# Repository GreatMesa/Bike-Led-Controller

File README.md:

# Bike LED Controller
This project is sponsored by JLCPCB

## Introduction
The goal of this project is to add more customizability to bike lights. When I was looking though lights for my bike I found that there was a limited amount of colors and patterns I could use. I wanted to create lights and controllers so I could have a better understanding of what was going on in the controller in terms of current consumption and speed of the bike, things that also were not present in other controllers. In this project, I designed a custom bike ring + a custom led controller board so that I could have a greater level of control.

## Custom LED Ring
For the ring, I decided to split the base and top  of the ring into 8 seperate segments. This was due to the size of the ring being way to big for my bike & in terms of the print time & assembely ease, 8 segments seemed to do the best in those 2 categories. 

For the bottom, in order to connect the segments together, I decided to designed them so they would have a insert slot + a segment that goes into it. For the top, I ended up coating it in a layer of FLEX-SEAL in order to act as a water reppelent + a diffusior once I sanded it down to a degree. Here is one fully assmebled ring in action:

### LED Ring GIF

## Custom LED Controller
For the LED contoller, I had multiple goals in mine. The main goal I had was the ability for the contoller to convert a higher voltage input to a stable 5V. To do this, I used the TPS566238RQFR buck converter to convert the input voltage (designed for 2S) into 5V. I also used a AMS1117 to convert the 5V supply into 3.3V for the digital IC's and the ESP32. Speaking of digital IC's, I used 5 in this design, a INA236 to meausre the voltage, current, & power output of the controller, a TMP117 to measure the tempature of the board / enclousre enviroment, a BMI270 to measure the speed of the bike for custom effects, a SN74LVC2T45DCUR to convert the ESP32's 3.3V logic into a usable 5V logic level for the LED, and last but not least the CP2102N to allow communication between the USB pherephial and the ESP32 via UART. Here are the schematics, PCB layouts, & the 3D view.

### Schematic

### PCB Layout

### 3D View

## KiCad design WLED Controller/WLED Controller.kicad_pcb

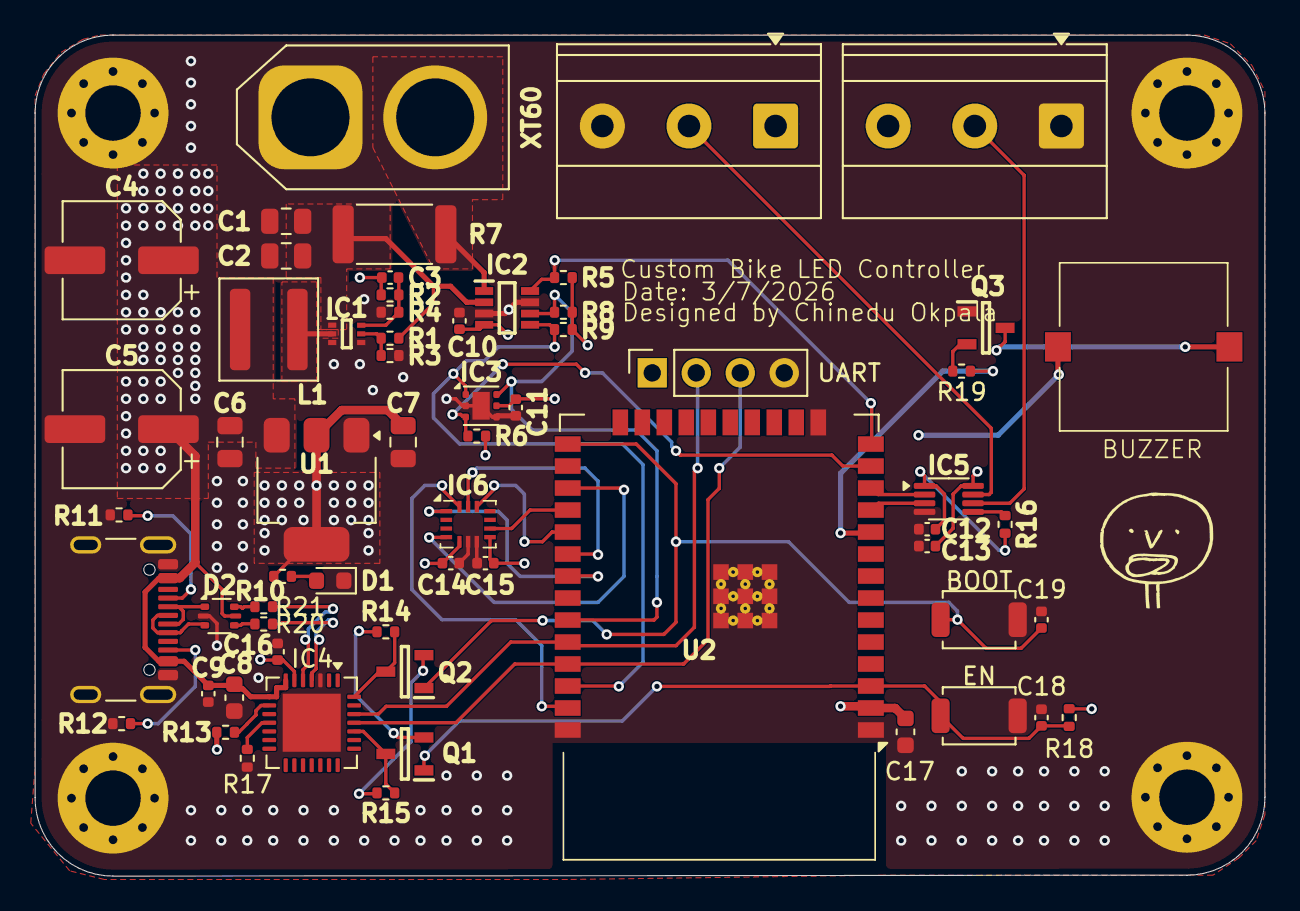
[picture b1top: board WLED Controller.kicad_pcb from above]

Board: 4 copper layers, 71.0 x 48.6 mm, 66 parts (0 on the bottom side), 45 nets.

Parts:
BOOT: Boot Switch; SW_SPST_TS-1088-xR025
BZ1: Buzzer; CMI97050380SMTTR
C1, C2: 22uF; C_0805_2012Metric
C3: 33pF; C_0402_1005Metric
C4, C5: 68uF; CP_Elec_6.3x5.8
C6, C7: 10uF; C_0805_2012Metric
C8, C17: 4.7uF; C_0603_1608Metric
C9, C10, C11, C12, C13, C14, C15, C16, C18, C19: 100nF; C_0402_1005Metric
D1: LED; LED_0603_1608Metric
D2: TVS; SOT-666
EN: Enable Switch; SW_SPST_TS-1088-xR025
H1: M1; MountingHole_3.2mm_M3_Pad_Via
H2: M2; MountingHole_3.2mm_M3_Pad_Via
H3: M3; MountingHole_3.2mm_M3_Pad_Via
H4: M4; MountingHole_3.2mm_M3_Pad_Via
IC1: TPS565242DRLR; SOTFL50P160X60-6N
IC2: INA236AIDDFR; SOP65P280X110-8N
IC3: TMP117xxDRV; WSON-6-1EP_2x2mm_P0.65mm_EP1x1.6mm
IC4: CP2102N-Axx-xQFN28; QFN-28-1EP_5x5mm_P0.5mm_EP3.35x3.35mm
IC5: SN74LVC2T45DCUR; VSSOP-8_2.3x2mm_P0.5mm
IC6: BMI270; Bosch_LGA-14_3x2.5mm_P0.5mm
J1, J2: Conn_01x03; TerminalBlock_Phoenix_MKDS-1,5-3_1x03_P5.00mm_Horizontal
J3: USB_C_Receptacle_USB2.0_14P; USB_C_Receptacle_GCT_USB4105-xx-A_16P_TopMnt_Horizontal
L1: 2.2uH; L_Coilcraft_XAL5030-XXX
Q1, Q2, Q3: NPN; SOT95P240X115-3N
R1: 100k; R_0402_1005Metric
R2: 220k; R_0402_1005Metric
R3: 33.3k; R_0402_1005Metric
R4: 30k; R_0402_1005Metric
R5, R6, R8, R9, R16, R17: 4.7k; R_0402_1005Metric
R7: 0.01; R_2512_6332Metric
R10, R13, R14, R15, R18: 10k; R_0402_1005Metric
R11, R12: 5.1k; R_0402_1005Metric
R19: 1k; R_0402_1005Metric
R20, R21: 22; R_0402_1005Metric
U1: AP1117-33; SOT-223-3_TabPin2
U2: ESP32-WROOM-32E
UART: UART; PinSocket_1x04_P2.54mm_Vertical
XT60: XT-60; AMASS_XT60-F_1x02_P7.20mm_Vertical

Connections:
+3.3V: BZ1.1 (+), C7.1, C10.1, C11.1, C12.1, C14.1, C15.1, C16.1, C17.1, IC2.4 (VS), IC3.5 (V+), IC4.6 (VDD), IC5.1 (VCCA), IC6.5 (VDDIO), IC6.8 (VDD), R5.1, R6.1, R8.1, R9.1, R10.1, R13.1, R16.1, R18.2, U1.2 (VO), U2.2 (VDD), UART.1
+5V: C3.1, C4.1, C5.1, C6.1, C8.1, C9.1, C13.1, D2.5 (VBUS), IC4.7 (VREGIN), IC4.8 (VBUS), IC5.8 (VCCB), J1.1, J2.3, J3.A4 (VBUS), J3.A9 (VBUS), J3.B4 (VBUS), J3.B9 (VBUS), L1.2, R2.1, U1.3 (VI)
+7.4V: C1.1, C2.1, IC1.1 (VIN), IC2.2 (IN-), R1.1, R7.2
/FB: C3.2, IC1.6 (FB), R2.2, R4.1
/SW: IC1.2 (SW), L1.1
BOOT: BOOT.1, C19.1, Q2.1 (C), U2.25 (IO0)
BUZZER+: BZ1.2 (-), Q3.3 (E)
BUZZER-PWM: R19.2, U2.10 (IO25)
D+: D2.4 (I/O2), R20.1
D-: D2.6 (I/O1), R21.2
DATA-3V3-1: IC5.2 (A1), U2.12 (IO27)
DATA-3V3-2: IC5.3 (A2), U2.11 (IO26)
DATA-5V-1: IC5.7 (B1), J1.2
DATA-5V-2: IC5.6 (B2), J2.2
DR+: IC4.4 (D+), R20.2
DR-: IC4.5 (D-), R21.1
DTR: IC4.28 (~DTR), Q2.3 (E), R14.2
EN: C18.1, EN.1, Q1.1 (C), R18.1, U2.3 (EN)
ESP32-RX: IC4.26 (TXD), U2.34 (RXD0/IO3), UART.2
ESP32-TX: IC4.25 (RXD), U2.35 (TXD0/IO1), UART.3
GND: BOOT.2, C1.2, C2.2, C4.2, C5.2, C6.2, C7.2, C8.2, C9.2, C10.2, C11.2, C12.2, C13.2, C14.2, C15.2, C16.2, C17.2, C18.2, C19.2, D1.1 (K), D2.2 (GND), EN.2, H1.1 (1_1), H2.1 (1_1), H3.1 (1_1), H4.1 (1_1), IC1.3 (GND), IC1.4 (AGND), IC2.3 (GND), IC2.7 (A0), IC3.2 (GND), IC3.4 (ADD0), IC3.7, IC4.3 (GND), IC4.29 (GND), IC5.4 (GND), IC6.6 (GNDIO), IC6.7 (GND), J1.3, J2.1, J3.A1 (GND), J3.A12 (GND), J3.B1 (GND), J3.B12 (GND), J3.S1 (SHIELD), Q3.1 (C), R3.2, R4.2, R11.2, R12.2, R17.1, U1.1 (GND), U2.1 (GND), U2.15 (GND), U2.38 (GND), U2.39 (GND), UART.4, XT60.1
I2C-SCL: IC2.5 (SCL), IC3.1 (SCL), R9.2, U2.36 (IO22)
I2C-SDA: IC2.6 (SDA), IC3.6 (SDA), R8.2, U2.33 (IO21)
IMU-CS: IC6.12 (CSB), U2.29 (IO5)
IMU-INT1: IC6.4 (INT1), U2.27 (IO16)
IMU-INT2: IC6.9 (INT2), U2.28 (IO17)
IMU-MISO: IC6.1 (SDO), U2.31 (IO19)
IMU-MOSI: IC6.14 (SDx), U2.37 (IO23)
IMU-SCLK: IC6.13 (SCx), U2.30 (IO18)
INA236-ALERT: IC2.8 (~ALERT), R5.2, U2.14 (IO12)
unnamed: D1.2 (A), R10.2
unnamed: IC1.5 (EN), R1.2, R3.1
unnamed: IC4.9 (~RST), R13.2
unnamed: IC4.11 (~SUSPEND), R17.2
unnamed: IC5.5 (DIR), R16.2
unnamed: J3.A5 (CC1), R11.1
unnamed: J3.B5 (CC2), R12.1
unnamed: Q1.2 (B), R14.1
unnamed: Q2.2 (B), R15.2
unnamed: Q3.2 (B), R19.1
RTS: IC4.24 (~RTS), Q1.3 (E), R15.1
TMP117-ALERT: IC3.3 (ALERT), R6.2, U2.13 (IO14)
USB-N: D2.1 (I/O1), J3.A7 (D-), J3.B7 (D-)
USB-P: D2.3 (I/O2), J3.A6 (D+), J3.B6 (D+)
VCC: IC2.1 (IN+), R7.1, XT60.2

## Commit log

2026-05-13 Added all initial files
2026-06-11 Added current software + hardware
2026-06-18 bumbiclat
2026-06-18 redo
2026-06-18 Remove accidental history submodule
